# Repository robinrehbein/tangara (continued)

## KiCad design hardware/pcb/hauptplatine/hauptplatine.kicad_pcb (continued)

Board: 4 copper layers, 153 parts (16 on the bottom side), 104 nets, no tracks yet.

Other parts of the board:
FID1, FID2, FID3, FID4, FID5, FID6: Fiducial; Fiducial_1mm_Mask2mm

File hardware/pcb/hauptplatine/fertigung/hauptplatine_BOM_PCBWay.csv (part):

Item,Designator,Qty,Manufacturer,Mfg Part #,Description,Package,Type,LCSC #,DigiKey #,Herkunft,Bestueckung
1,C23,1,Murata,GRM188R61A105KA61D,"1uF -  0603 statt 0805 (Hoehe <= 1,0 mm fuer die Oberseite)",0603,SMD,,,angepasst,ja
2,"C24,C25,C27,C32,C35,C42",6,Murata,GRM188R61A106KE69,"10uF -  0603 statt 0805 (Hoehe <= 1,0 mm fuer die Oberseite)",0603,SMD,,,angepasst,ja
3,C29,1,Murata,GRM32EC70J107ME15K,100uF - ,1210,SMD,,,Tangara,ja
4,"C30,C34,C37",3,Murata,GCM188R71C104KA37J,0.1uF - ,0603,SMD,,,Tangara,ja
5,C100,1,Samsung,CL05A105KA5NQNC,1uF - EN-Kondensator (Espressif: RC 10 k / 1 uF),0402,SMD,C52923,,Espressif,ja
6,C101,1,Murata,GRM188R60J226MEA0,22uF - Espressif: 22 uF am Modul-3V3,0603,SMD,,,Espressif,ja
7,"C102,C103",2,Samsung,CL05B104KO5NNNC,100nF - Espressif: 100 nF am Modul-3V3,0402,SMD,C1525,,Espressif,ja
8,"C104,C110,C114,C131,C133,C257,C258,C259,C262",9,Samsung,CL05B104KO5NNNC,100nF - MAX17048 VDD,0402,SMD,C1525,,neu,ja
9,"C111,C113",2,Murata,GRM188R61A106KE69,10uF - Boost Eingang,0603,SMD,,,neu,ja
10,C112,1,Murata,GRM188R60J226MEA0,22uF - Boost Ausgang (25 V X5R),0603,SMD,,,neu,ja
11,"C130,C132",2,Murata,GRM155R60J106ME05D,10uF - Display-Versorgung VCI/VDDIO (Waveshare C27),0402,SMD,,,neu,ja
12,"C240,C241,C242,C253",4,Samsung,CL05B104KO5NNNC,100nF - VL,0402,SMD,C1525,,Cirrus,ja
13,"C243,C244,C247,C248,C249,C250,C251,C252",8,Murata,GRM155R60J225ME15D,"2.2uF - VA (X5R, 6,3 V)",0402,SMD,,,Cirrus,ja
14,"C245,C246",2,,"(15 uF X5R >= 6,3 V 0603, Typ nach Verfuegbarkeit)",15uF - FILT+ (X5R),0603,SMD,,,Cirrus,ja
15,C254,1,Murata,GRM188R60J475KE19D,4.7uF - VP (X5R),0603,SMD,,,Cirrus,ja
16,"C255,C256",2,Murata,GRM1555C1H100JA01D,10pF - Quarz-Lastkondensator C0G (nach Abschnitt 5.3 abstimmen),0402,SMD,,,Cirrus,ja
17,C260,1,Samsung,CL05A105KA5NQNC,1uF - LDO Eingang,0402,SMD,C52923,,neu,ja
18,C261,1,Murata,GRM155R60J225ME15D,2.2uF - LDO Ausgang,0402,SMD,,,neu,ja
19,D4,1,Nexperia,BAT54C,BAT54C - ,SOT-23,SMD,,,Tangara,ja
20,D10,1,Nexperia,BAT54C,BAT54C - Entkopplung ID -> Gate-Knoten (Totbatterie: ID ohne 3V3 hochohmig),SOT-23,SMD,,,neu,ja
21,FB1,1,Murata,BLM15AG121SN1D,"BLM15 120R - Ferritperle: VA/VCP vom digitalen 1,8-V-Zweig trennen (Datenblatt Abschnitt 8.1: VA, VCP aus sauberer Versorgung)",0402,SMD,,,Cirrus,ja
22,J1,1,Same Sky (CUI Devices),SJ-43504-SMT-TR,"SJ-43504-SMT-TR - Klinke 5,0 mm hoch (Tangara: SJ-3506-SMT, 6,0 mm), Mid-Mount im Randausschnitt der Platine, Pads auf der Rueckseite; Spitzenschalter -> HP_DETECT (HPDETECT_INV im DAC setzen)","3,5 mm 4-polig, 5,0 mm hoch",SMD,,,angepasst,ja
23,J4,1,Molex,104031-0811,microSD - microSD statt Vollformat-SD (Tangara: Hirose DM1AA-SF-PEJ(82)); SDMMC 4 Bit direkt am S31 (IO35...IO40) statt SPI + Multiplexer,microSD Push-Push,SMD,,WM6357DKR-ND,angepasst,ja
24,J6,1,GCT,USB4510-03-1-A,USB - ,GCT_USB4510-03-1-A_REVA,THT,,,Tangara,ja
25,J20,1,Hirose,FH12-30S-0.5SH(55),"FH12-30S-0.5SH(55) - Display-FPC-Stecker, 30 Pin 0,5 mm (Waveshare 2,06""-Board J3); Typ (Kontaktseite oben/unten, FPC-Dicke) gegen das gekaufte Panel pruefen","FPC 30 Pin 0,5 mm, 1,0 mm hoch",SMD,,,neu,ja
26,J21,1,Hirose,FH12-6S-0.5SH(55),"FH12-6S-0.5SH(55) - Klickrad-Modul v2 (AT42QT2120 0x1C + DRV2605L 0x5A), gleicher Stecker wie auf hardware/pcb/klickrad (J1); Pin 5 = CHANGE, Pin 6 = Reserve","FFC 6 Pin 0,5 mm, 1,0 mm hoch",SMD,,,neu,ja
27,L20,1,Murata,DFE201610E-1R0M=P2,"1uH - 1 uH 2,0 x 1,6 x 1,0 mm (TPS61023 Tab. 8-2: Saettigungsstrom >= 3 A!); Typ und Landmuster (hier L_0805 als Naeherung) vor Bestellung pruefen",2016,SMD,,,neu,ja
28,Q1,1,Nexperia,PMV48XPA2R,PMV48XPA2R - ,TSOT-23,SMD,,,Tangara,ja
29,"Q10,Q11,Q20",3,Diodes Inc.,2N7002T-7-F,"2N7002T - zieht Q1-Gate nach GND (Sink-Betrieb); aus, wenn ID low (Host)",SOT-523,SMD,,,neu,ja
30,R1,1,,0.1W 5%,10k - ,0603,SMD,,,Tangara,ja
31,"R4,R43",2,Yageo,AC0603JR-0710KL,"10k - Taster-Vorwiderstand (Tangara: 100 k); bei Tastendruck KEY_LOCK ca. 0,9 x SYS_POWER",0603,SMD,,,angepasst,ja
32,R7,1,Yageo,AC0603FR-131ML ,1M - ,0603,SMD,,,Tangara,ja
33,"R9,R11,R12,R34,R35,R37,R38,R41,R57,R61",10,Yageo,AC0603JR-0710KL,10k - ,0603,SMD,,,Tangara,ja
34,R36,1,Yageo,AC0603FR-07100KL,"100k - PROG2 hoch = USB-Eingangslimit 500 mA (Tangara: Pin vom SAMD21 gesteuert); hier Pull-up an 3V3, S31 kann ueberschreiben",0603,SMD,,,angepasst,ja
35,R39,1,Yageo,RC0603DR-071KL,1k - ,0603,SMD,,,Tangara,ja
36,"R100,R101",2,UNI-ROYAL,0402WGF1002TCE,10k - EN-Pull-up (Espressif: RC-Verzoegerung 10 k / 1 uF),0402,SMD,C25744,,Espressif,ja
37,"R102,R103",2,UNI-ROYAL,0402WGF0000TCE,0 - USB-HS D+: Platz fuer Serienwiderstand (Anfangswert 0 Ohm),0402,SMD,C17168,,Espressif,ja
38,R110,1,,,887k - VBUS_DET: ca. 900 k in Reihe laut Datenblatt (887 k E96; 0402),0402,SMD,,,neu,ja
39,"R111,R115,R119,R122,R130,R131,R132,R136,R246",9,UNI-ROYAL,0402WGF1002TCE,10k - INT_N Pull-up,0402,SMD,C25744,,neu,ja
40,"R112,R113,R114,R135,R244,R245",6,UNI-ROYAL,0402WGF1003TCE,"100k - ID Pull-up (open drain, low = Geraet angeschlossen, wir sind Quelle)",0402,SMD,C25741,,neu,ja
41,R116,1,,,"390k - FB-Teiler: 0,595 V x (1 + 390k/51k) = 5,15 V",0402,SMD,,,neu,ja
42,R117,1,,,51k - FB-Teiler,0402,SMD,,,neu,ja
43,R118,1,,,"49.9k - Stromlimit ca. 520 mA (Datenblatt: IOS 490-550 mA bei 49,9 k)",0402,SMD,,,neu,ja
44,"R120,R121",2,UNI-ROYAL,0402WGF2201TCE,2.2k - I2C Pull-up (Klickrad-Modul bestueckt keine),0402,SMD,C25879,,neu,ja
45,"R134,R248,R249",3,UNI-ROYAL,0402WGF4701TCE,4.7k - FPC-Pin 21 (Waveshare DSI_PWR_EN) fest high,0402,SMD,C25900,,neu,ja
46,"R200,R202",2,Yageo,AC0603FR-07100KL,100k - KEY_LOCK Pull-down (Taster offen = low),0603,SMD,,,neu,ja
47,R201,1,Yageo,AC0603JR-0710KL,"10k - Serienwiderstand zum S31-GPIO (SYS_POWER bis 5 V, GPIO 3,3 V)",0603,SMD,,,neu,ja
48,"R240,R241",2,UNI-ROYAL,0402WGF0000TCE,"0 - Quarz 22,5792 MHz an XTI",0402,SMD,C17168,,neu,ja
49,"R242,R243",2,UNI-ROYAL,0402WGF0000TCE,"0 - Quarz 24,576 MHz an XTI (DNP)",0402,SMD,C17168,,neu,NICHT BESTUECKEN (DNP)
50,R247,1,,,200k - EN-Pull-up PCA9306 (200 k laut Datenblatt),0402,SMD,,,neu,ja
51,SW1,1,Omron,B3U-3000P,B3U-3000P - Ein/Aus-Taster statt Schiebeschalter JS102011SAQN (Tangara): drueckt SYS_POWER auf KEY_LOCK -> LDO_EN,"3,0 x 2,5 x 1,2",SMD,C963349,,angepasst,ja
52,TP7,1,,,BAT - ,TestPoint_Pad_D1.0mm,SMD,,,Tangara,ja
53,U3,1,Diodes Inc.,D5V0L2B3T-7,"D5V0L2B3T-7 - ESD-Schutz Kopfhoerer-Ausgaenge (Tangara 1:1, Netze angepasst)",SOT-523,SMD,,,Tangara,ja
54,U4,1,Texas Instruments,TLV75733PDRVR,"TLV75733PDRV - 3V3-LDO 1 A (Tangara: TLV75533PDBV, 500 mA) im flachen WSON-6 (0,8 mm), Pinbelegung DRV nach Datenblatt SBVS322C; Spitzen bis ca. 375 mA S31-Senden + Display + DAC-LDO",WSON-6 2 x 2,SMD,,,angepasst,ja
55,U5,1,ProTek Devices,PE1605C4A6,PE1605C4A6 - ,SOT-23-6,SMD,,,Tangara,ja
56,U10,1,Microchip,MCP73871-2CCI/ML,MCP73871 - ,QFN-20-1EP_4x4mm_P0.5mm_EP2.5x2.5mm,SMD,,,Tangara,ja
57,U12,1,Texas Instruments,TUSB320LAIRWBR,"TUSB320LAI - USB-C DRP-Controller, I2C 0x47 (ADDR=GND), ersetzt Tangara BD91N01NUX (nur Sink)","X2QFN-12 1,6 x 1,6",SMD,C132554,296-TUSB320LAIRWBRCT-ND,neu,ja
58,U15,1,Espressif,ESP32-S31-WROOM-1-N16R16V,"ESP32-S31-WROOM-1-N16R16V - WLAN 6, Bluetooth 5.4 (Classic + LE Audio), USB 2.0 HS OTG, 16 MB Flash, 16 MB PSRAM (Datenblatt v0.5 PRELIMINARY); Tangara: ESP32-WROVER-E","Modul 18 x 25,5 x 3,1",SMD,,,neu,ja
59,U16,1,Texas Instruments,TPS22948DCKR,TPS22948 - ,SOT65P210X110-6N,SMD,,,Tangara,ja
60,U17,1,Cirrus Logic,CS43131-CNZR,"CS43131-CNZR - DAC mit Class-H-Kopfhoererverstaerker (125 dB DNR an 32 Ohm), I2C, I2S-Master (statt Tangara WM8523 + INA1620 + TPS65133)",QFN-40 5 x 5,SMD,,598-CS43131-CNZRCT-ND,neu,ja
61,U20,1,Texas Instruments,TPS61023DRLR,"TPS61023DRL - Boost 5,1 V aus SYS_POWER (Schalterstrom 3,7 A)",SOT-563,SMD,C919459,296-TPS61023DRLRCT-ND,neu,ja
62,U21,1,Texas Instruments,TPS2553DRVR,"TPS2553DRV - Lastschalter mit Strombegrenzung (49,9 k = ca. 520 mA), WSON-Gehaeuse 0,8 mm hoch (Pinbelegung nach Datenblatt SLVS...)",WSON-6 2 x 2,SMD,,,neu,ja
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
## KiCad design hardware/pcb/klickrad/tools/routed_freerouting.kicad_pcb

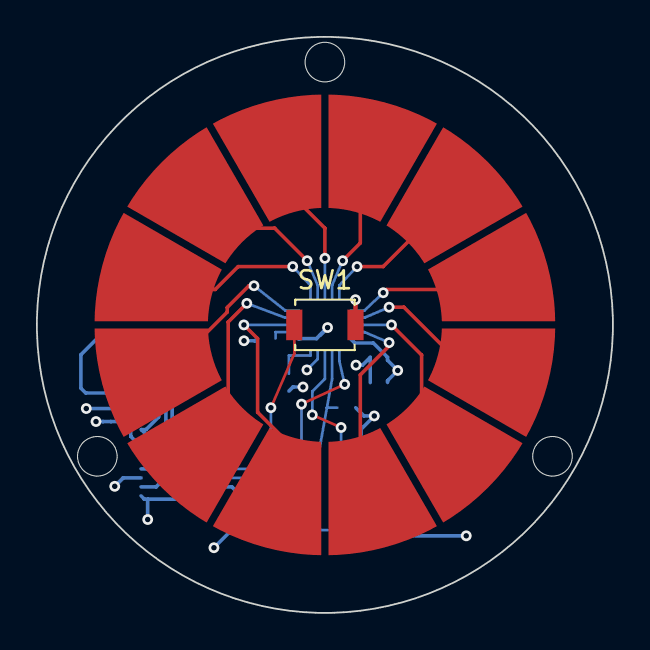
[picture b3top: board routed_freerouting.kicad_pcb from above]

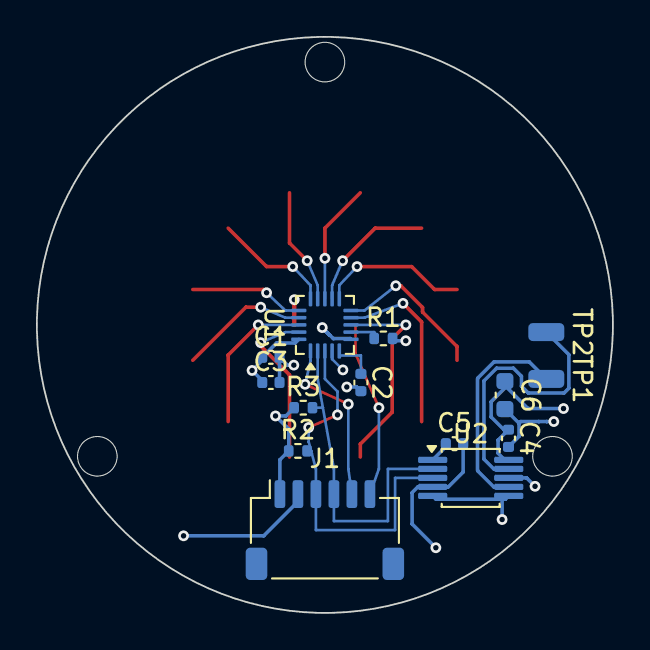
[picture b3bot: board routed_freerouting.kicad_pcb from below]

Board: 4 copper layers, 32.0 x 32.0 mm, 30 parts (14 on the bottom side), 23 nets.

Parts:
C1, C2: 0.1uF; C_0402_1005Metric
C3, C4, C5: 1uF; C_0402_1005Metric
C6: 10uF; C_0603_1608Metric
H1, H2, H3: M2; MountingHole_2.2mm_NPTH
J1: SM06B-SRSS-TB; JST_SH_SM06B-SRSS-TB_1x06-1MP_P1.00mm_Horizontal
R1: 75k; R_0402_1005Metric
R2, R3: 4.7k; R_0402_1005Metric
SEG1: Touch1; SEG1
SEG2: Touch2; SEG2
SEG3: Touch3; SEG3
SEG4: Touch4; SEG4
SEG5: Touch5; SEG5
SEG6: Touch6; SEG6
SEG7: Touch7; SEG7
SEG8: Touch8; SEG8
SEG9: Touch9; SEG9
SEG10: Touch10; SEG10
SEG11: Touch11; SEG11
SEG12: Touch12; SEG12
SW1: B3U-1000P; SW_SPST_B3U-1000P
TP1: LRA+; SolderWirePad_1x01_SMD_1x2mm
TP2: LRA-; SolderWirePad_1x01_SMD_1x2mm
U1: MPR121QR2; QFN-20_3x3mm_P0.4mm_noEP
U2: DRV2605LDGSR; MSOP-10_3x3mm_P0.5mm

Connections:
3V3: C1.1, C3.1, C4.1, C6.1, J1.1, R2.1, R3.1, U1.4, U1.20, U2.5, U2.6, U2.10
BTN: J1.6, SW1.1
ELE0: SEG9.1, U1.8
ELE1: SEG8.1, U1.9
ELE2: SEG7.1, U1.10
ELE3: SEG6.1, U1.11
ELE4: SEG5.1, U1.12
ELE5: SEG4.1, U1.13
ELE6: SEG3.1, U1.14
ELE7: SEG2.1, U1.15
ELE8: SEG1.1, U1.16
ELE9: SEG12.1, U1.17
ELE10: SEG11.1, U1.18
ELE11: SEG10.1, U1.19
GND: C1.2, C2.2, C3.2, C4.2, C5.2, C6.2, J1.2, R1.2, SW1.2, U1.6, U2.4, U2.8
INT: J1.5, U1.1
LRA_N: TP2.1, U2.9
LRA_P: TP1.1, U2.7
REG: C5.1, U2.1
REXT: R1.1, U1.7
SCL: J1.4, R3.2, U1.2, U2.2
SDA: J1.3, R2.2, U1.3, U2.3
VREG: C2.1, U1.5

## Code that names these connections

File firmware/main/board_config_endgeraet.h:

/* Copyright 2026 Nano-Player-Projekt
 * SPDX-License-Identifier: GPL-3.0-only */
#pragma once
/**
 * Board-Profil "Endgeraet": Hauptplatine Rev. 3b mit ESP32-S31-WROOM-1-N16R16V
 * (Quelle: hardware/pcb/hauptplatine/README.md "GPIO-Pruefung ... und Belegung", TEILE.md Rev. 3b).
 *
 * STATUS: nur vorbereitet. Nicht fuer den S31 gebaut (IDF 5.4.2 kennt das Ziel nicht), nicht auf Hardware
 * getestet. Die Pin-Zuordnung der Platine ist selbst "ungeprueft gegen das endgueltige Datenblatt (v0.5,
 * vorlaeufig)". Mit [offen] markierte Werte sind nicht eindeutig und stehen auch in
 * docs/FIRMWARE-PORTIERUNG.md Abschnitt "Board-Profil Endgeraet".
 *
 * Gegenueber dem Prototyp entfallen: IO-Expander TCA9554, Touch-Reset per Expander, AXP2101, ES8311, QMI8658,
 * PCF85063, Mitteltasten-Pin BTN (Stecker-Pin 6 ist Reserve), Latenz-Messpunkte (keine freien Pads vergeben),
 * eigener Wheel-Bus. Die Lader-Steuerung (SEL/PROG2) ist fest verdrahtet, keine GPIOs (IO14/IO15 frei).
 */
#include "driver/gpio.h"
#include "driver/i2c_master.h"

/* ---- Display: 2,06" AMOLED 410 x 502, CO5300, QSPI (nicht der Prototyp-Wert 368 x 448) ---- */
#define BOARD_LCD_HOST       SPI2_HOST          /* [offen] S31-Hostname/Pad-Eignung gegen IDF 6 pruefen */
#define BOARD_LCD_H_RES      410
#define BOARD_LCD_V_RES      502
#define BOARD_LCD_CS         GPIO_NUM_49
#define BOARD_LCD_SCLK       GPIO_NUM_48
#define BOARD_LCD_D0         GPIO_NUM_11
#define BOARD_LCD_D1         GPIO_NUM_10
#define BOARD_LCD_D2         GPIO_NUM_9
#define BOARD_LCD_D3         GPIO_NUM_51
#define BOARD_LCD_RST_GPIO   GPIO_NUM_19        /* LCD_RST direkt am S31 (100 k Pull-up), kein Expander */
#define BOARD_LCD_TE_GPIO    GPIO_NUM_12        /* Tearing-Effect, in Phase 1 nicht benutzt */
#define BOARD_TP_INT_GPIO    GPIO_NUM_50        /* Display-Touch-Interrupt, Phase 1 nicht benutzt */
/* [offen] X-/Y-Versatz des 2,06"-Panels (Waveshare-2.06-Beispiel nicht ausgewertet); 0 bis zur Pruefung.
 * Das 1,8"-Prototyp-Panel braucht 0x10, das hier ist ein anderes Modul. */
#define BOARD_LCD_GAP_X_V2   0
#define BOARD_LCD_GAP_X_V1   0
/* DSI_PWR_EN (FPC-Pin 21) liegt per 4,7 k fest auf 3V3, TP_RESET (Pin 9) per 10 k: nichts zu schalten. */

/* ---- I2C [Platine: IO6 = SDA, IO7 = SCL; Pull-ups R120/R121 (2,2 k) auf der Hauptplatine] ---- */
#define BOARD_I2C_PORT       I2C_NUM_0
#define BOARD_I2C_SDA        GPIO_NUM_6
#define BOARD_I2C_SCL        GPIO_NUM_7
#define BOARD_I2C_FREQ_HZ    400000
#define BOARD_I2C_INTERNAL_PULLUP 0
/* Adressen am Bus: 0x1C AT42QT2120, 0x5A DRV2605L (Klickrad), 0x36 MAX17048, 0x47 TUSB320LAI (ADDR = GND),
 * Display-Touch [offen: Controller/Adresse des 2,06"-Moduls nicht geklaert], CS43131 0x30..0x33 [offen, aus
 * docs/AUDIO.md, mit [?] markiert] liegt hinter dem Pegelwandler PCA9306 (U30; Segment DAC_SDA/DAC_SCL, EN-Knoten
 * PCA_EN = 200 k nach 3V3 + 100 pF, kein GPIO). Kein TCA9554 (0x20), kein 0x15/0x38 von Waveshare. */
#define BOARD_ADDR_MAX17048  0x36
#define BOARD_ADDR_TUSB320   0x47
#define BOARD_ADDR_CS43131   0x30   /* [offen] 0x30..0x33 */
#define BOARD_ADDR_TOUCH_V2  0x15   /* [offen] nur fuer board_touch_is_v2(); Controller des 2,06"-Moduls ungeklaert */
#define BOARD_ADDR_TOUCH_V1  0x38
#define BOARD_HAS_TCA9554    0

/* ---- Klickrad-Modul v2 (Stecker J21: 1 3V3, 2 GND, 3 SDA, 4 SCL, 5 CHANGE, 6 Reserve) ---- */
#define WHEEL_ADDR_MPR121    0x5B   /* v1, am Endgeraet nicht vorgesehen */
#define WHEEL_ADDR_QT2120    0x1C
#define WHEEL_ADDR_DRV2605L  0x5A
#define WHEEL_INT_GPIO       GPIO_NUM_0    /* WHEEL_INT = CHANGE, LP-GPIO IO0 (Weckquelle), R136 10 k Pull-up auf der Platine */
#define WHEEL_BTN_GPIO       GPIO_NUM_NC   /* Pin 6 ist Reserve; Mitteltaste nur kapazitiv (QT2120 Taste 3) */
#define WHEEL_BTN_USED       0
/* Eigener Wheel-Bus gibt es nicht (Kconfig-Option nur beim Prototyp). */
#define WHEEL_I2C_PORT2      I2C_NUM_1
#define WHEEL_I2C2_SDA       GPIO_NUM_NC
#define WHEEL_I2C2_SCL       GPIO_NUM_NC

/* ---- Versorgung / weitere Signale der Platine (Phase 1: nur der Power-Latch wird benutzt) ---- */
/* Power-Latch: SW1 schaltet nur kurz ein, der S31 muss SYS_PWR_EN frueh im Start halten, sonst faellt die
 * Versorgung nach dem Loslassen wieder ab. [offen] Aktivpegel nicht aus der README ablesbar, high angenommen;
 * Schaltplan (Netz SYS_PWR_EN, Q/LDO_EN) vor dem ersten Einschalten pruefen. */
#define BOARD_PWR_HOLD_GPIO   GPIO_NUM_4
#define BOARD_PWR_HOLD_LEVEL  1
#define BOARD_KEY_LOCK_GPIO   GPIO_NUM_5    /* Ein/Aus-Taster lesen (LP-GPIO, Weckquelle), Phase 1 nicht benutzt */
#define BOARD_FG_ALRT_GPIO    GPIO_NUM_1    /* MAX17048 ALRT, nicht benutzt */
#define BOARD_HOST_EN_GPIO    GPIO_NUM_2    /* Host-VBUS an/aus, nicht benutzt (Reset-Zustand: aus) */
#define BOARD_TUSB_ID_GPIO    GPIO_NUM_3
#define BOARD_TUSB_INT_GPIO   GPIO_NUM_18
#define BOARD_CHG_STAT1_GPIO  GPIO_NUM_13   /* MCP73871; SEL/PROG2 fest verdrahtet, keine GPIO */
#define BOARD_CHG_STAT2_GPIO  GPIO_NUM_16
#define BOARD_CHG_PG_GPIO     GPIO_NUM_17
/* DAC-Reset mit Sicherung (Rev. 3b): Gate von Q20 liegt per Pull-up an 3V3 => Pin offen/high = DAC in RESET,
 * low = RESET freigegeben; Q21/Q22 halten RESET ohne 3V3 ebenfalls low. Phase 1 laesst den Pin unberuehrt
 * (DAC bleibt im Reset, kein Audio). Beim spaeteren Audio-Code: erst 3V3/1,8 V stabil, dann IO20 auf low. */
#define BOARD_DAC_RESET_GPIO  GPIO_NUM_20
#define BOARD_DAC_INT_GPIO    GPIO_NUM_21   /* aktiv low, 10 k Pull-up */
#define BOARD_I2S_BCLK_GPIO   GPIO_NUM_22   /* S31 = I2S-Slave, DAC liefert Takt (kein MCLK) */
#define BOARD_I2S_LRCK_GPIO   GPIO_NUM_23
#define BOARD_I2S_DOUT_GPIO   GPIO_NUM_24
#define BOARD_SD_CD_GPIO      GPIO_NUM_25
#define BOARD_SD_VDD_EN_GPIO  GPIO_NUM_42
/* SDMMC Slot 2: feste Pads IO35..IO40 (D0..D3, CLK, CMD; Zuordnung in der README, nicht hier).
 * Nicht benutzen (Strapping/Boot/Debug): IO36, IO37, IO60, IO61 (BOOT, Taster SW2), IO33/IO34 (USB-Serial/JTAG),
 * TX0/RX0, EN (Taster SW3). BOOT/EN-Taster brauchen keine Firmware. */
/* Keine Latenz-Messpunkte vergeben (Kconfig-Option nur beim Prototyp). */
#define PROBE_STEP_GPIO      GPIO_NUM_NC
#define PROBE_HAPTIC_GPIO    GPIO_NUM_NC
